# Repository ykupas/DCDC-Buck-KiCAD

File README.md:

# DCDC-Buck-KiCAD

DC-DC buck converter KiCAD project using OpAmps to compensate and control switching. KiCAD v10 used. Circuit simulated in [this](https://github.com/ykupas/DCDC-Buck-Converter) repository.

## Schematics

## Plant

## Input

## Output

## Controller

## Compensator

## PCB

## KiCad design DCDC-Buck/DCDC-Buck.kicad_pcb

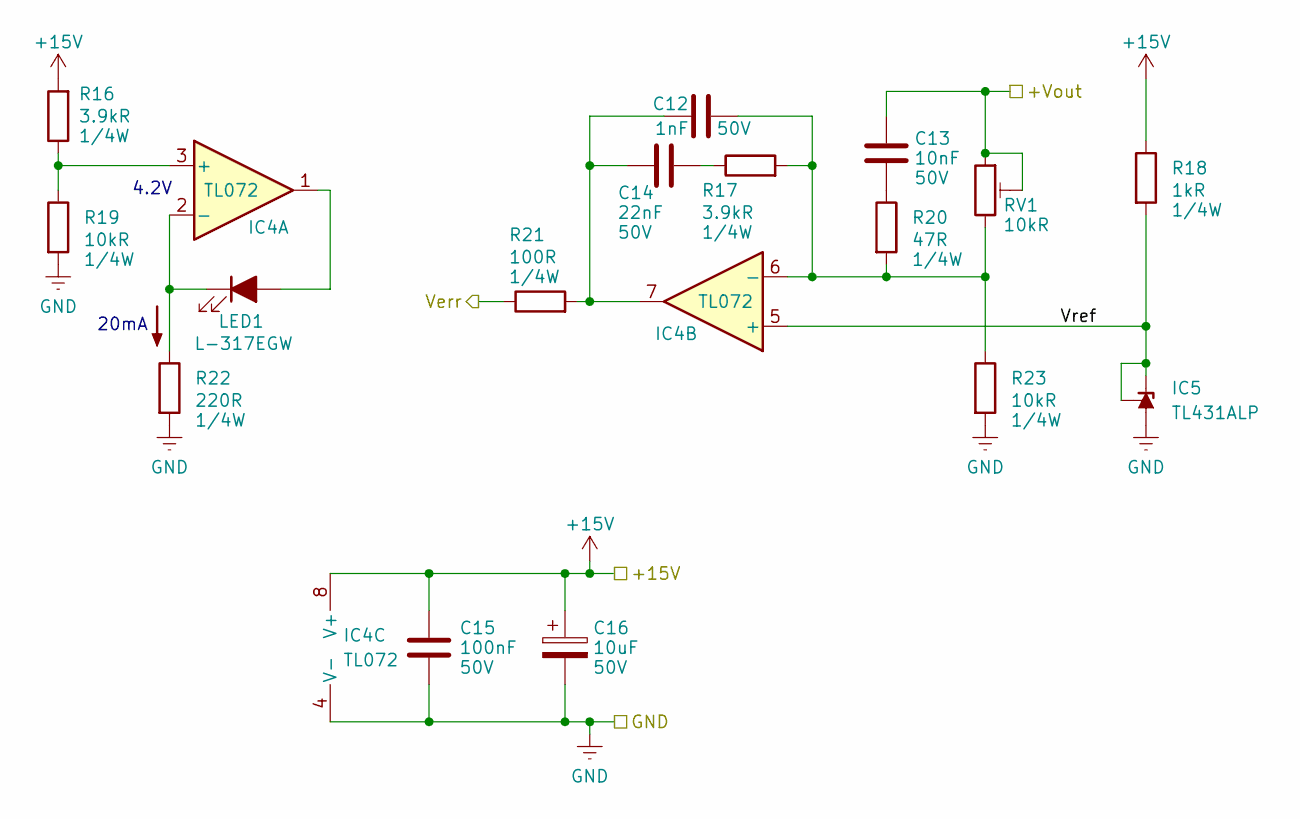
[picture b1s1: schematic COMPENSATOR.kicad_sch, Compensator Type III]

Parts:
C12: 1nF; C_Disc_D3.0mm_W2.0mm_P2.50mm; Voltage 50V
C13: 10nF; C_Disc_D3.0mm_W2.0mm_P2.50mm; Voltage 50V
C14: 22nF; C_Disc_D3.0mm_W2.0mm_P2.50mm; Voltage 50V
C15: 100nF; C_Disc_D3.0mm_W2.0mm_P2.50mm; Voltage 50V
C16: 10uF; C_Radial_D6.3mm_H11.0mm_P2.50mm; Voltage 50V
IC4: TL072; DIP-8_W7.62mm_LongPads
IC5: TL431ALP; TO-92_Inline
LED1: L-317EGW; LED_D3.0mm
R16, R17: 3.9kR; R_Axial_DIN0207_L6.3mm_D2.5mm_P7.62mm_Horizontal
R18: 1kR; R_Axial_DIN0207_L6.3mm_D2.5mm_P7.62mm_Horizontal
R19, R23: 10kR; R_Axial_DIN0207_L6.3mm_D2.5mm_P7.62mm_Horizontal
R20: 47R; R_Axial_DIN0207_L6.3mm_D2.5mm_P7.62mm_Horizontal
R21: 100R; R_Axial_DIN0207_L6.3mm_D2.5mm_P7.62mm_Horizontal
R22: 220R; R_Axial_DIN0207_L6.3mm_D2.5mm_P7.62mm_Horizontal
RV1: 10kR; Potentiometer_Bourns_3296W_Vertical

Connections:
+15V: C15.1, C16.1, IC4.8 (V+), R16.2, R18.1; also elsewhere on the board
+Vout: C13.1, RV1.1, RV1.2; also elsewhere on the board
/COMPENSATOR/Verr: R21.1; also elsewhere on the board
/COMPENSATOR/Vref: IC4.5 (+), IC5.1 (REF), IC5.3 (K), R18.2
GND: C15.2, C16.2, IC4.4 (V-), IC5.2 (A), R19.2, R22.2, R23.2; also elsewhere on the board
unnamed: C12.1, C14.1, IC4.7, R21.2
unnamed: C13.2, R20.1
unnamed: C14.2, R17.1
unnamed: IC4.3 (+), R16.1, R19.1
unnamed: IC4.2 (-), LED1.1 (K), R22.1
unnamed: C12.2, IC4.6 (-), R17.2, R20.2, R23.1, RV1.3
unnamed: IC4.1, LED1.2 (A)

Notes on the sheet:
4.2V
20mA

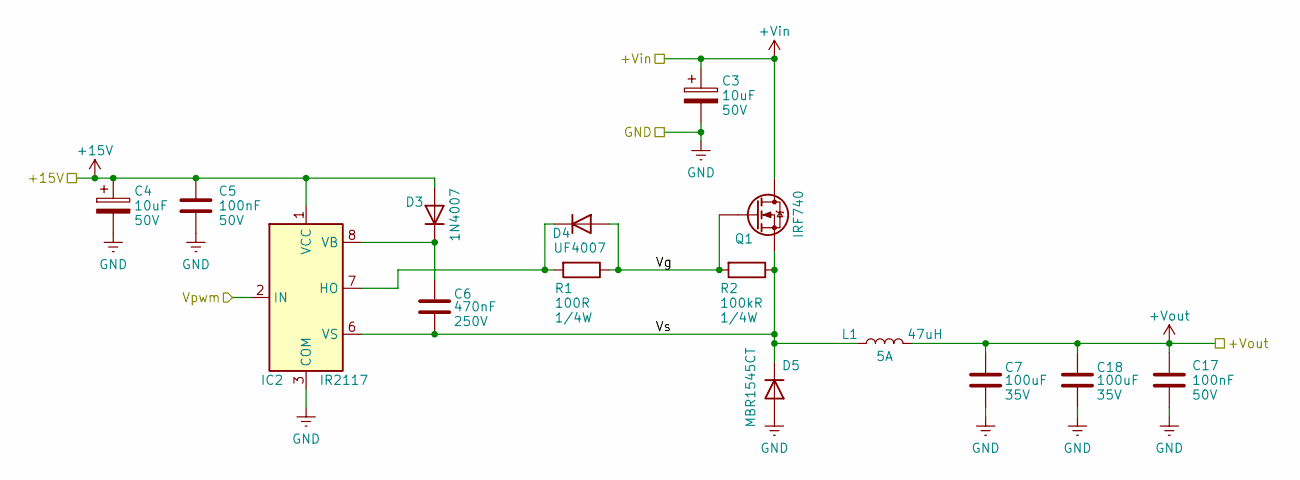
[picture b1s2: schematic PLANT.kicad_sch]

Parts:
C3, C4: 10uF; C_Radial_D6.3mm_H11.0mm_P2.50mm; Voltage 50V
C5, C17: 100nF; C_Disc_D3.0mm_W2.0mm_P2.50mm; Voltage 50V
C6: 470nF; C_Rect_L13.0mm_W4.0mm_P10.00mm_FKS3_FKP3_MKS4; Voltage 250V
C7, C18: 100uF; CP_Radial_Tantal_D8.0mm_P5.00mm; Voltage 35V
D3: 1N4007; D_DO-41_SOD81_P10.16mm_Horizontal
D4: UF4007; D_DO-41_SOD81_P10.16mm_Horizontal
D5: MBR1545CT; TO-220-3_Vertical
IC2: IR2117; DIP-8_W7.62mm_LongPads
L1: 47uH; L_Toroid_Vertical_L25.4mm_W14.7mm_P12.20mm_Vishay_TJ5
Q1: IRF740; TO-220-3_Vertical
R1: 100R; R_Axial_DIN0207_L6.3mm_D2.5mm_P7.62mm_Horizontal
R2: 100kR; R_Axial_DIN0207_L6.3mm_D2.5mm_P7.62mm_Horizontal

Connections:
+15V: C4.1, C5.1, D3.2 (A), IC2.1 (VCC); also elsewhere on the board
+Vin: C3.1, Q1.2 (D); also elsewhere on the board
+Vout: C7.1, C17.1, C18.1, L1.2; also elsewhere on the board
/CONTROLLER/Vpwm: IC2.2 (IN); also elsewhere on the board
/PLANT/Vg: D4.2 (A), Q1.1 (G), R1.1, R2.2
/PLANT/Vs: C6.2, D5.2 (K), IC2.6 (VS), L1.1, Q1.3 (S), R2.1
GND: C3.2, C4.2, C5.2, C7.2, C17.2, C18.2, D5.1 (A), D5.3 (A), IC2.3 (COM); also elsewhere on the board
unnamed: C6.1, D3.1 (K), IC2.8 (VB)
unnamed: D4.1 (K), IC2.7 (HO), R1.2

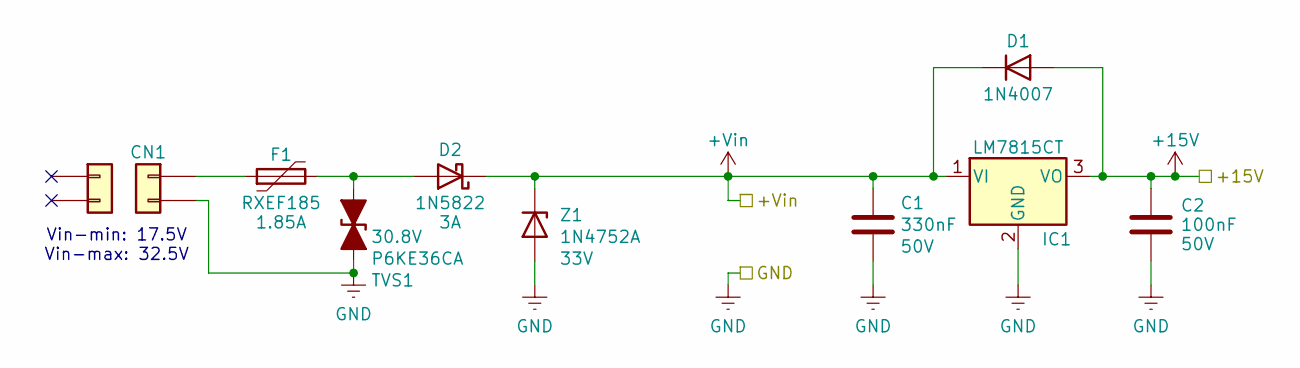
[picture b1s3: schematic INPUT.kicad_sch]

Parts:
C1: 330nF; C_Rect_L10.0mm_W5.0mm_P5.00mm_P7.50mm; Voltage 50V
C2: 100nF; C_Disc_D3.0mm_W2.0mm_P2.50mm; Voltage 50V
CN1: STLZ950GH; TerminalBlock_Phoenix_MKDS-1,5-2-5.08_1x02_P5.08mm_Horizont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
D1: 1N4007; D_DO-41_SOD81_P10.16mm_Horizontal
D2: 1N5822; D_DO-201AD_P15.24mm_Horizontal
EXT1: AKZ950
F1: RXEF185; Fuse_Bourns_MF-RHT1000
IC1: LM7815CT; TO-220-3_Vertical
TVS1: P6KE36CA; D_DO-15_P10.16mm_Horizontal; Breakdown Voltage 30.8V
Z1: 1N4752A; D_DO-41_SOD81_P10.16mm_Horizontal; Zener Voltage 33V

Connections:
+15V: C2.1, D1.2 (A), IC1.3 (VO); also elsewhere on the board
+Vin: C1.1, D1.1 (K), D2.1 (K), IC1.1 (VI), Z1.1 (K); also elsewhere on the board
GND: C1.2, C2.2, CN1.2, IC1.2 (GND), TVS1.2 (A2), Z1.2 (A); also elsewhere on the board
unnamed: CN1.1, F1.1
unnamed: D2.2 (A), F1.2, TVS1.1 (A1)

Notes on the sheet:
Vin-min: 17.5V Vin-max: 32.5V

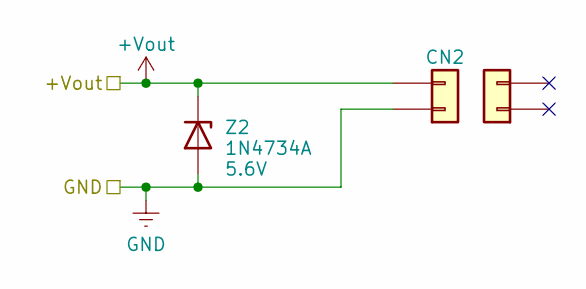
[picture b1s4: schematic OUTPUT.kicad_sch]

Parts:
CN2: STLZ950GH; TerminalBlock_Phoenix_MKDS-1,5-2-5.08_1x02_P5.08mm_Horizont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
EXT2: AKZ950
Z2: 1N4734A; D_DO-41_SOD81_P10.16mm_Horizontal; Zener Voltage 5.6V

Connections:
+Vout: CN2.2, Z2.1 (K); also elsewhere on the board
GND: CN2.1, Z2.2 (A); also elsewhere on the board

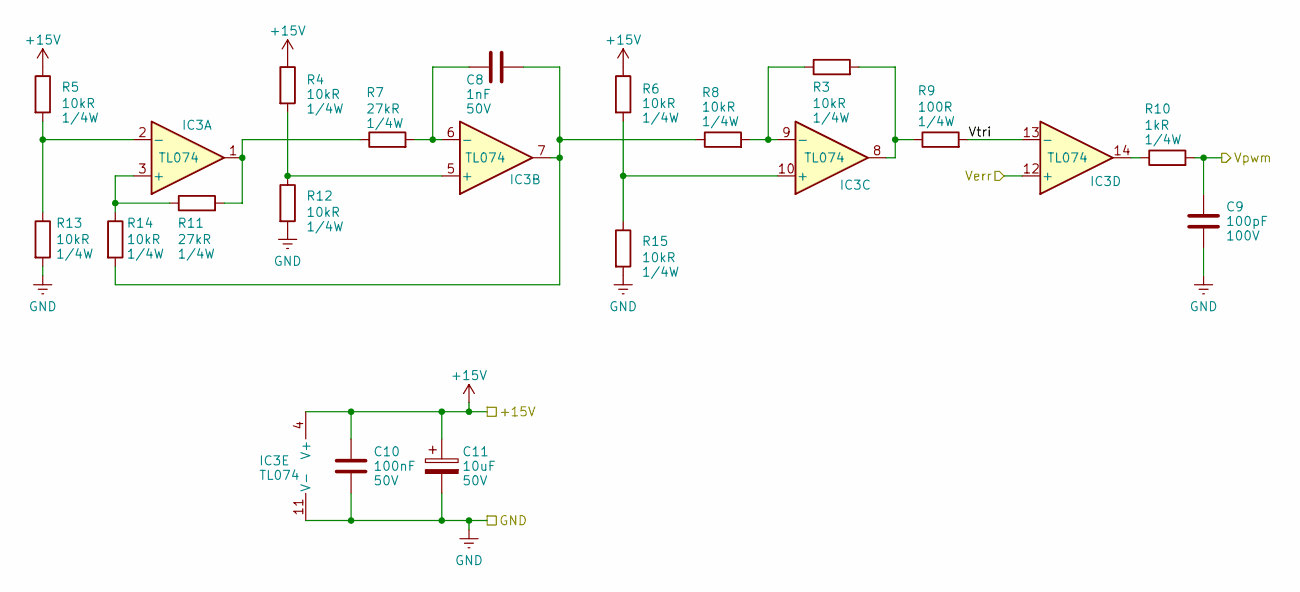
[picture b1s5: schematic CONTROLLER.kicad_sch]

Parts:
C8: 1nF; C_Rect_L7.2mm_W3.5mm_P5.00mm_FKS2_FKP2_MKS2_MKP2; Voltage 50V
C9: 100pF; C_Disc_D3.0mm_W2.0mm_P2.50mm; Voltage 100V
C10: 100nF; C_Disc_D3.0mm_W2.0mm_P2.50mm; Voltage 50V
C11: 10uF; C_Radial_D6.3mm_H11.0mm_P2.50mm; Voltage 50V
IC3: TL074; DIP-14_W7.62mm_LongPads
R3, R4, R5, R6, R8, R12, R13, R14, R15: 10kR; R_Axial_DIN0207_L6.3mm_D2.5mm_P7.62mm_Horizontal
R7, R11: 27kR; R_Axial_DIN0207_L6.3mm_D2.5mm_P7.62mm_Horizontal
R9: 100R; R_Axial_DIN0207_L6.3mm_D2.5mm_P7.62mm_Horizontal
R10: 1kR; R_Axial_DIN0207_L6.3mm_D2.5mm_P7.62mm_Horizontal

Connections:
+15V: C10.1, C11.1, IC3.4 (V+), R4.1, R5.1, R6.1; also elsewhere on the board
/COMPENSATOR/Verr: IC3.12 (+); also elsewhere on the board
/CONTROLLER/Vpwm: C9.1, R10.2; also elsewhere on the board
/CONTROLLER/Vtri: IC3.13 (-), R9.2
GND: C9.2, C10.2, C11.2, IC3.11 (V-), R12.2, R13.2, R15.2; also elsewhere on the board
unnamed: C8.2, IC3.7, R8.1, R14.2
unnamed: IC3.1, R7.1, R11.2
unnamed: IC3.8, R3.2, R9.1
unnamed: IC3.14, R10.1
unnamed: IC3.3 (+), R11.1, R14.1
unnamed: IC3.2 (-), R5.2, R13.1
unnamed: IC3.5 (+), R4.2, R12.1
unnamed: C8.1, IC3.6 (-), R7.2
unnamed: IC3.10 (+), R6.2, R15.1
unnamed: IC3.9 (-), R3.1, R8.2

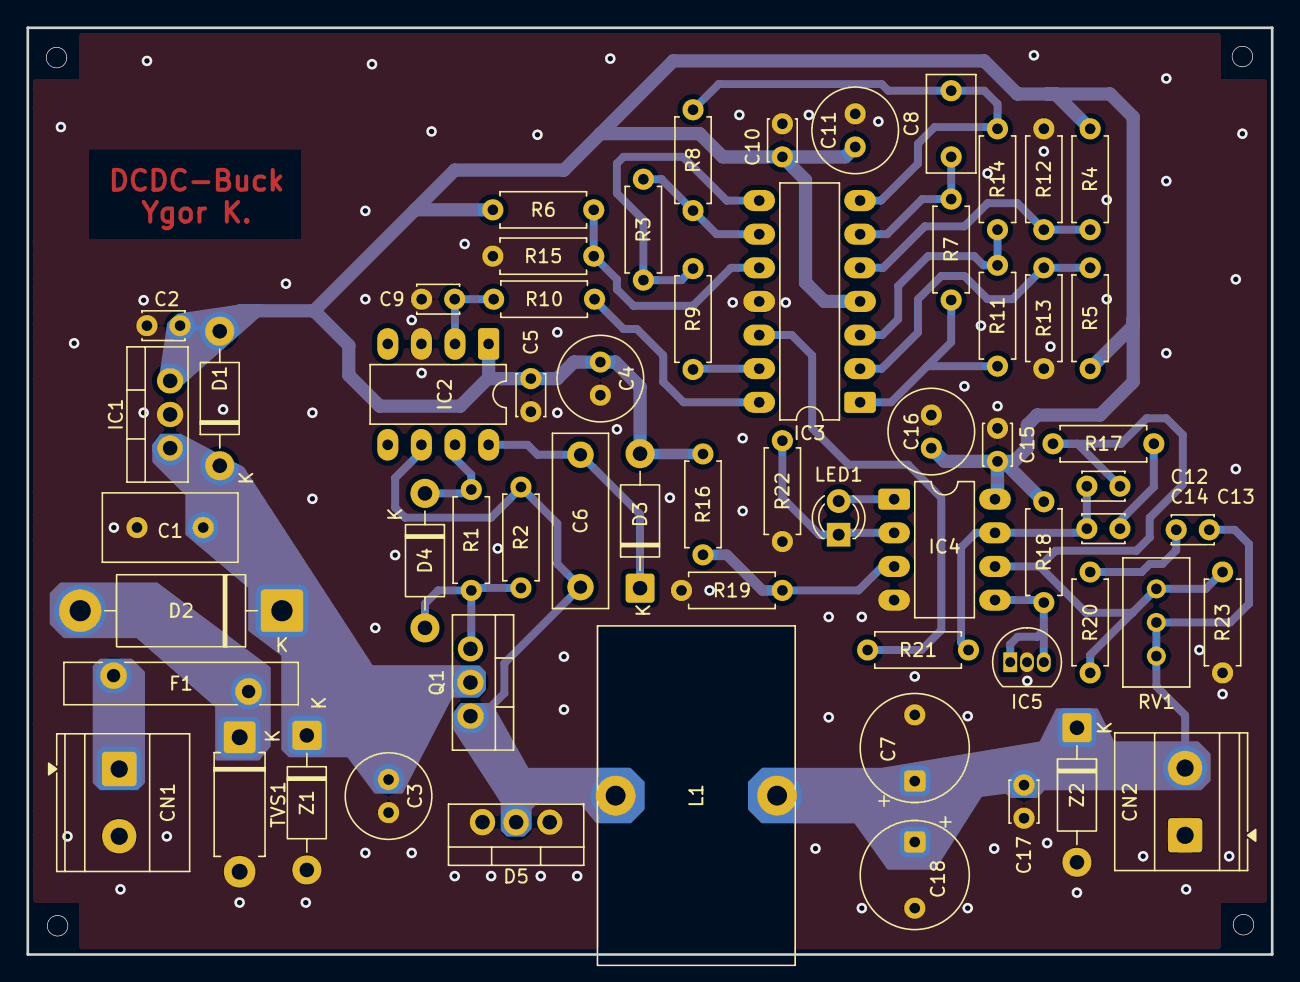
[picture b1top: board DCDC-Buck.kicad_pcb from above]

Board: 2 copper layers, 94.0 x 70.0 mm, 61 parts (0 on the bottom side), 31 nets.
